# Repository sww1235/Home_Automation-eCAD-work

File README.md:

# Home_Automation-eCAD-work
Contains Eagle and KiCAD files used for custom circuit boards involved in my home automation systems

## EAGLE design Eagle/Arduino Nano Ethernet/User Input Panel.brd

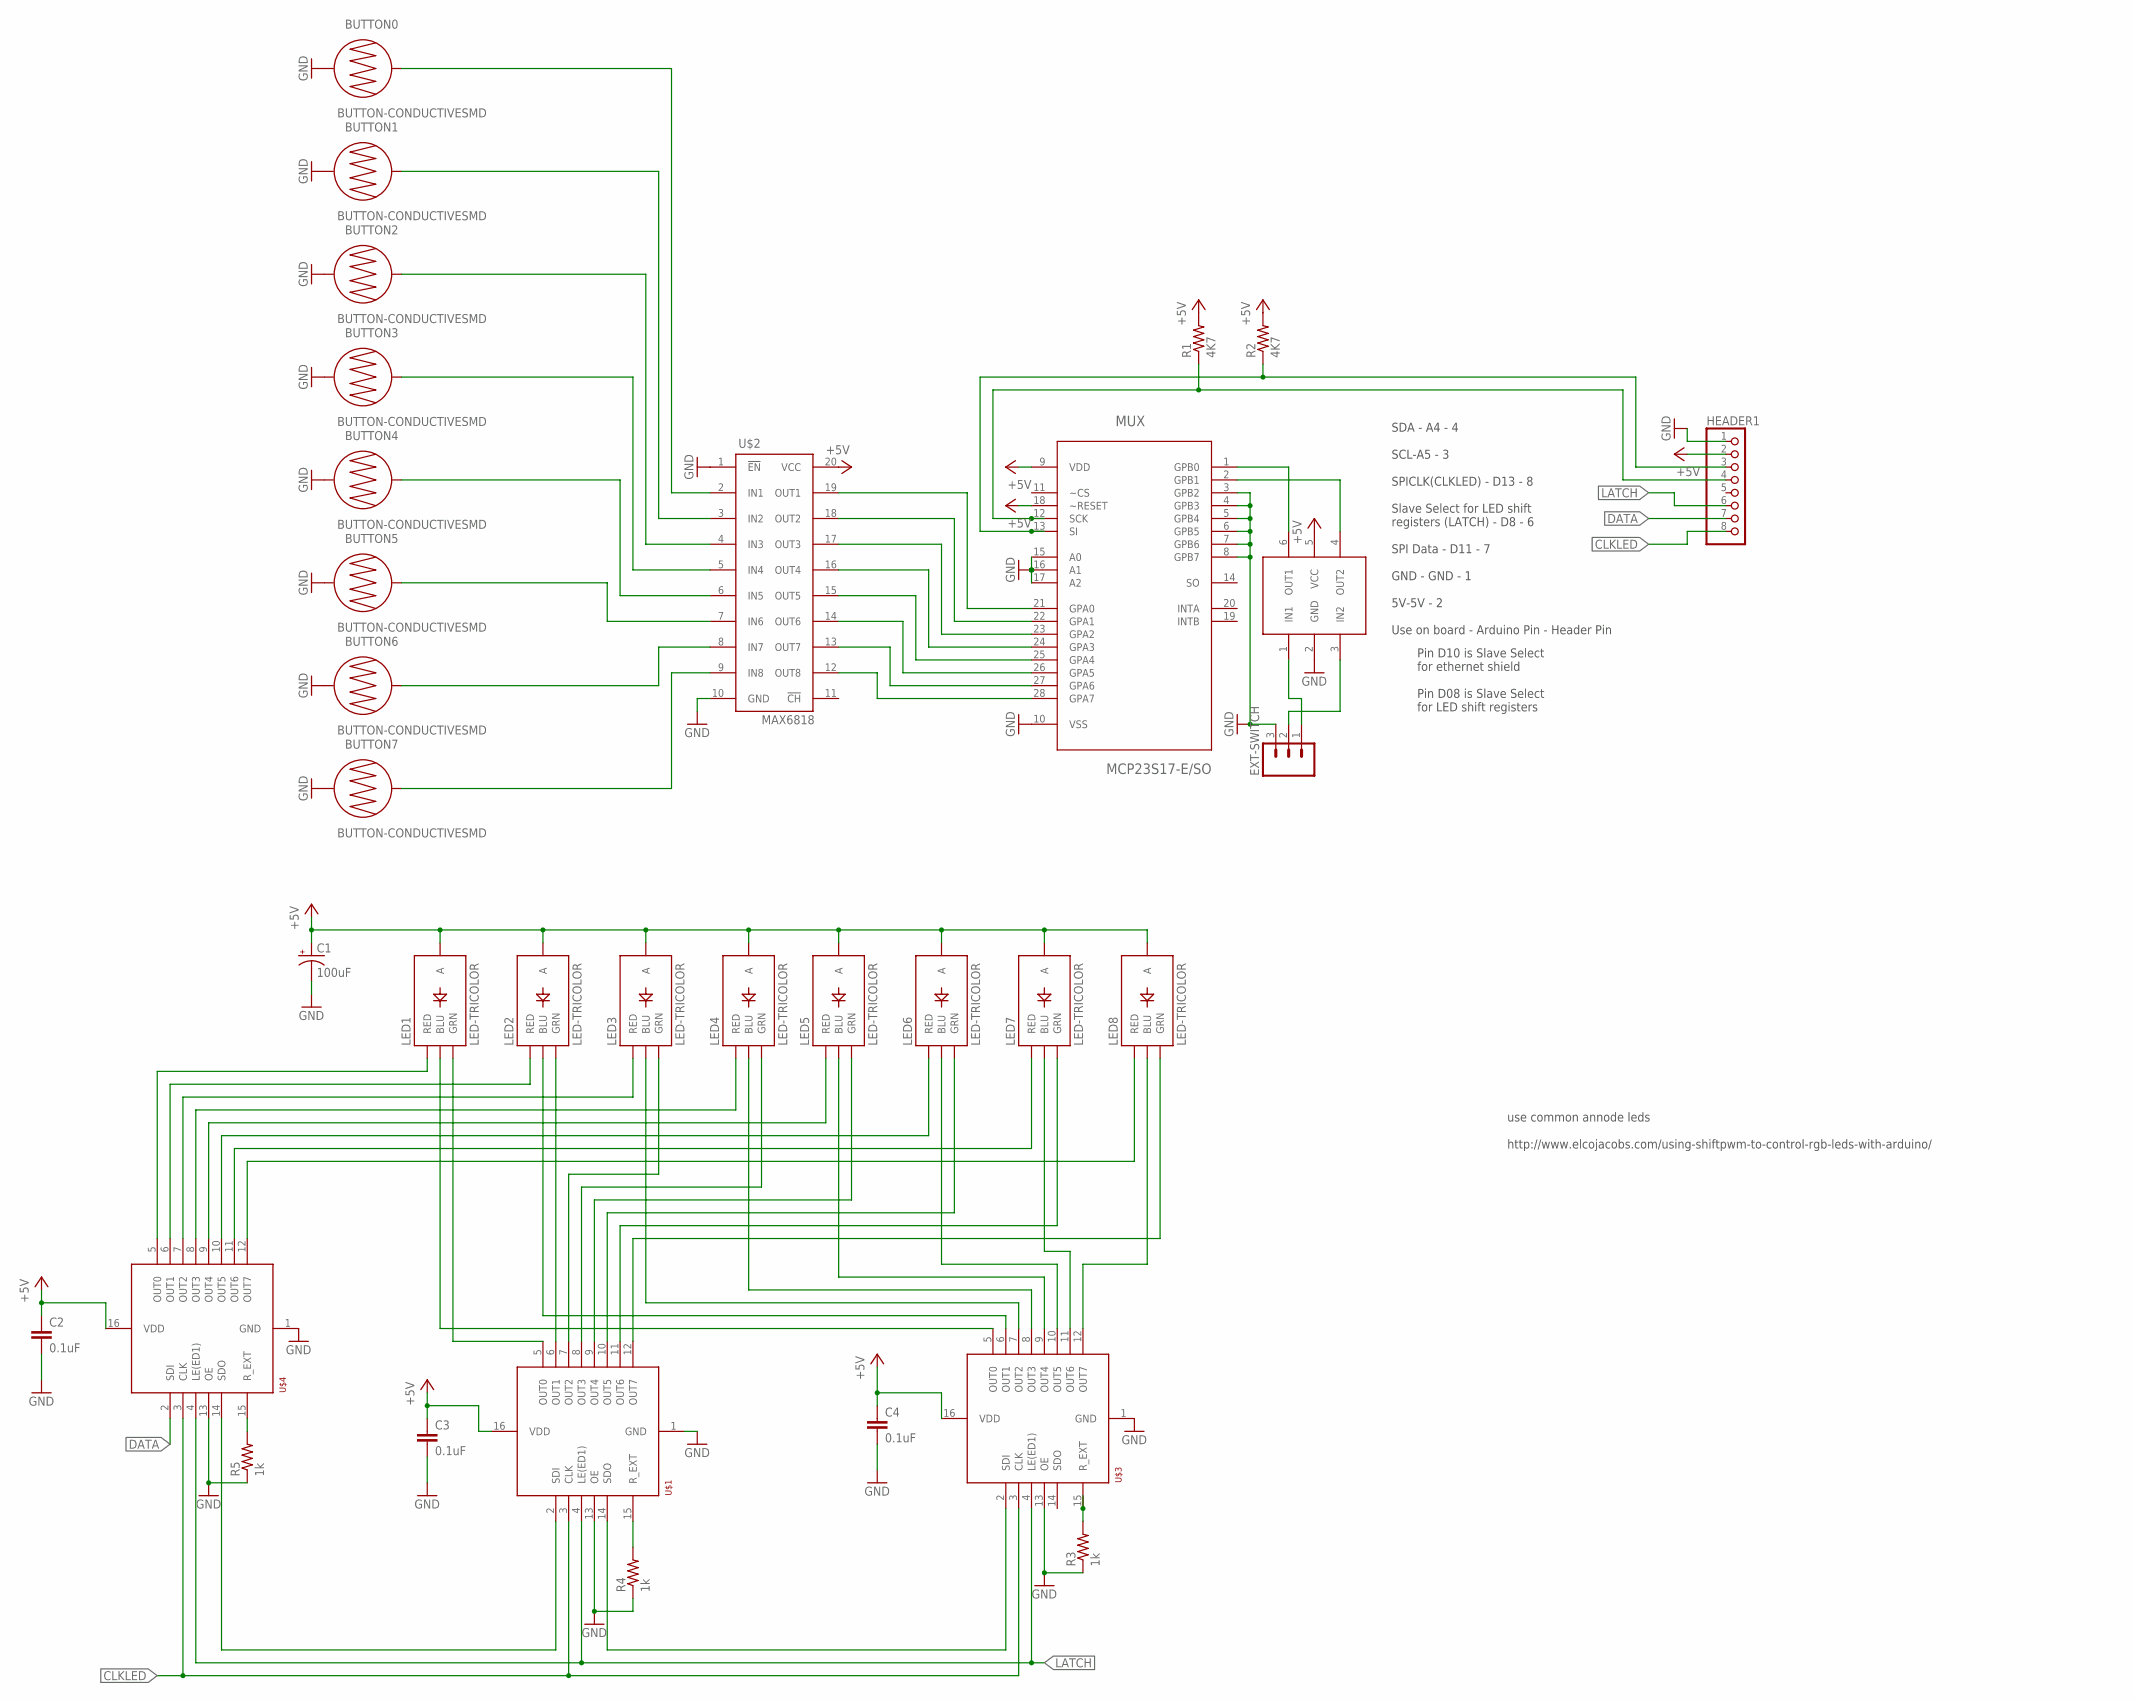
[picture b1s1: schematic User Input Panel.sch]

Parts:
BUTTON0, BUTTON1, BUTTON2, BUTTON3, BUTTON4, BUTTON5, BUTTON6, BUTTON7: BUTTON-CONDUCTIVESMD; BUTTON-CONDUCTIVE
C1: 100uF; EIA3216
C2, C3, C4: 0.1uF; 0402-CAP
EXT-SWITCH: M03-SCREW-5MM; SCREWTERMINAL-5MM-3
HEADER1: PINHD-1X8BIG; 1X08-BIG
LED1, LED2, LED3, LED4, LED5, LED6, LED7, LED8: LED-TRICOLOR; LED-TRICOLOR-SMD
MUX: MCP23S17-E/SO; SOIC127P030X265-28N
R1, R2: 4K7; 0204V
R3, R4, R5: 1k; 0402-RES
U$1, U$3, U$4: TLC5916/17; SOIC-16
U$2: MAX6818; SSOP20
U$5: MAX6817; SOT23-6L

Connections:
+5V: C1.A (+), C2.1, C3.1, C4.1, HEADER1.2, LED1.A, LED2.A, LED3.A, LED4.A, LED5.A, LED6.A, LED7.A, LED8.A, U$1.16 (VDD), U$2.20 (VCC), U$3.16 (VDD), U$4.16 (VDD), U$5.5 (VCC)
CLKLED: HEADER1.8, U$1.3 (CLK), U$3.3 (CLK), U$4.3 (CLK)
DATA: HEADER1.7, U$4.2 (SDI)
GND: BUTTON0.1, BUTTON1.1, BUTTON2.1, BUTTON3.1, BUTTON4.1, BUTTON5.1, BUTTON6.1, BUTTON7.1, C1.C (-), C2.2, C3.2, C4.2, EXT-SWITCH.3, HEADER1.1, MUX.3 (GPB2), MUX.4 (GPB3), MUX.5 (GPB4), MUX.6 (GPB5), MUX.7 (GPB6), MUX.8 (GPB7), MUX.10 (VSS), MUX.15 (A0), MUX.16 (A1), MUX.17 (A2), R3.1, R4.1, R5.1, U$1.1 (GND), U$1.13 (OE), U$2.1 (!EN!), U$2.10 (GND), U$3.1 (GND), U$3.13 (OE), U$4.1 (GND), U$4.13 (OE), U$5.2 (GND)
LATCH: HEADER1.6, U$1.4 (LE(ED1)), U$3.4 (LE(ED1)), U$4.4 (LE(ED1))
unnamed: MUX.28 (GPA7), U$2.12 (OUT8)
unnamed: MUX.24 (GPA3), U$2.16 (OUT4)
unnamed: MUX.26 (GPA5), U$2.14 (OUT6)
unnamed: MUX.25 (GPA4), U$2.15 (OUT5)
unnamed: MUX.27 (GPA6), U$2.13 (OUT7)
unnamed: MUX.23 (GPA2), U$2.17 (OUT3)
unnamed: MUX.22 (GPA1), U$2.18 (OUT2)
unnamed: MUX.21 (GPA0), U$2.19 (OUT1)
unnamed: HEADER1.4, MUX.12 (SCK), R1.1
unnamed: HEADER1.3, MUX.13 (SI), R2.1
unnamed: U$1.2 (SDI), U$4.14 (SDO)
unnamed: U$1.14 (SDO), U$3.2 (SDI)
unnamed: MUX.1 (GPB0), U$5.6 (OUT1)
unnamed: R5.2, U$4.15 (R_EXT)
unnamed: LED5.R (RED), U$4.9 (OUT4)
unnamed: LED6.R (RED), U$4.10 (OUT5)
unnamed: LED7.R (RED), U$4.11 (OUT6)
unnamed: R4.2, U$1.15 (R_EXT)
unnamed: R3.2, U$3.15 (R_EXT)
unnamed: LED1.R (RED), U$4.5 (OUT0)
unnamed: LED2.R (RED), U$4.6 (OUT1)
unnamed: LED3.R (RED), U$4.7 (OUT2)
unnamed: LED4.R (RED), U$4.8 (OUT3)
unnamed: LED8.R (RED), U$4.12 (OUT7)
unnamed: LED1.G (GRN), U$1.5 (OUT0)
unnamed: LED2.G (GRN), U$1.6 (OUT1)
unnamed: LED3.G (GRN), U$1.7 (OUT2)
unnamed: LED4.G (GRN), U$1.8 (OUT3)
unnamed: LED5.G (GRN), U$1.9 (OUT4)
unnamed: LED6.G (GRN), U$1.10 (OUT5)
unnamed: LED7.G (GRN), U$1.11 (OUT6)
unnamed: LED8.G (GRN), U$1.12 (OUT7)
unnamed: LED2.B (BLU), U$3.6 (OUT1)
unnamed: LED1.B (BLU), U$3.5 (OUT0)
unnamed: LED3.B (BLU), U$3.7 (OUT2)
unnamed: LED4.B (BLU), U$3.8 (OUT3)
unnamed: LED5.B (BLU), U$3.9 (OUT4)
unnamed: LED6.B (BLU), U$3.10 (OUT5)
unnamed: LED7.B (BLU), U$3.11 (OUT6)
unnamed: LED8.B (BLU), U$3.12 (OUT7)
unnamed: MUX.2 (GPB1), U$5.4 (OUT2)
unnamed: BUTTON0.2, U$2.2 (IN1)
unnamed: BUTTON1.2, U$2.3 (IN2)
unnamed: BUTTON2.2, U$2.4 (IN3)
unnamed: BUTTON3.2, U$2.5 (IN4)
unnamed: BUTTON4.2, U$2.6 (IN5)
unnamed: BUTTON5.2, U$2.7 (IN6)
unnamed: BUTTON7.2, U$2.9 (IN8)
unnamed: BUTTON6.2, U$2.8 (IN7)
unnamed: EXT-SWITCH.1, U$5.1 (IN1)
unnamed: EXT-SWITCH.2, U$5.3 (IN2)
VCC: MUX.9 (VDD), MUX.18 (~RESET), R1.2, R2.2

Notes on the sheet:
use common annode leds http://www.elcojacobs.com/using-shiftpwm-to-control-rgb-leds-with-arduino/
Pin D10 is Slave Select for ethernet shield Pin D08 is Slave Select for LED shift registers
SDA - A4 - 4 SCL-A5 - 3 SPICLK(CLKLED) - D13 - 8 Slave Select for LED shift registers (LATCH) - D8 - 6 SPI Data - D11 - 7 GND - GND - 1 5V-5V - 2 Use on board - Arduino Pin - Header Pin

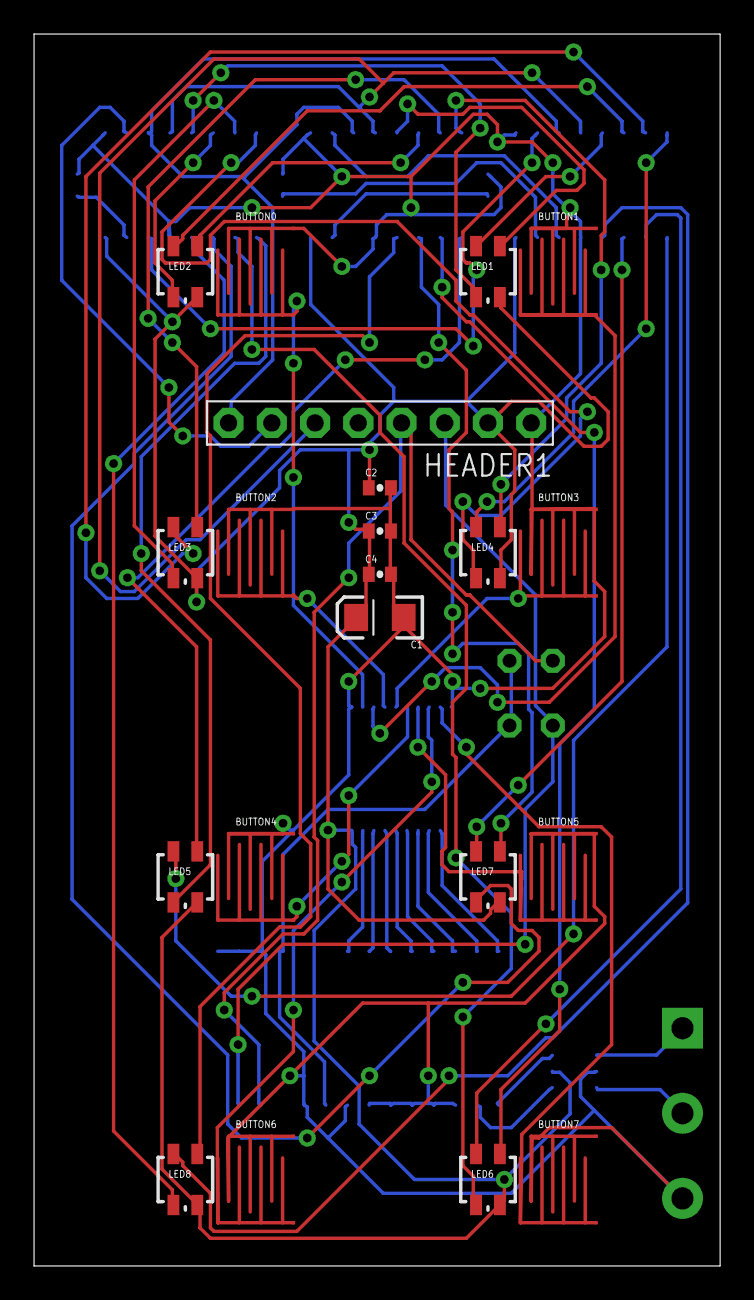
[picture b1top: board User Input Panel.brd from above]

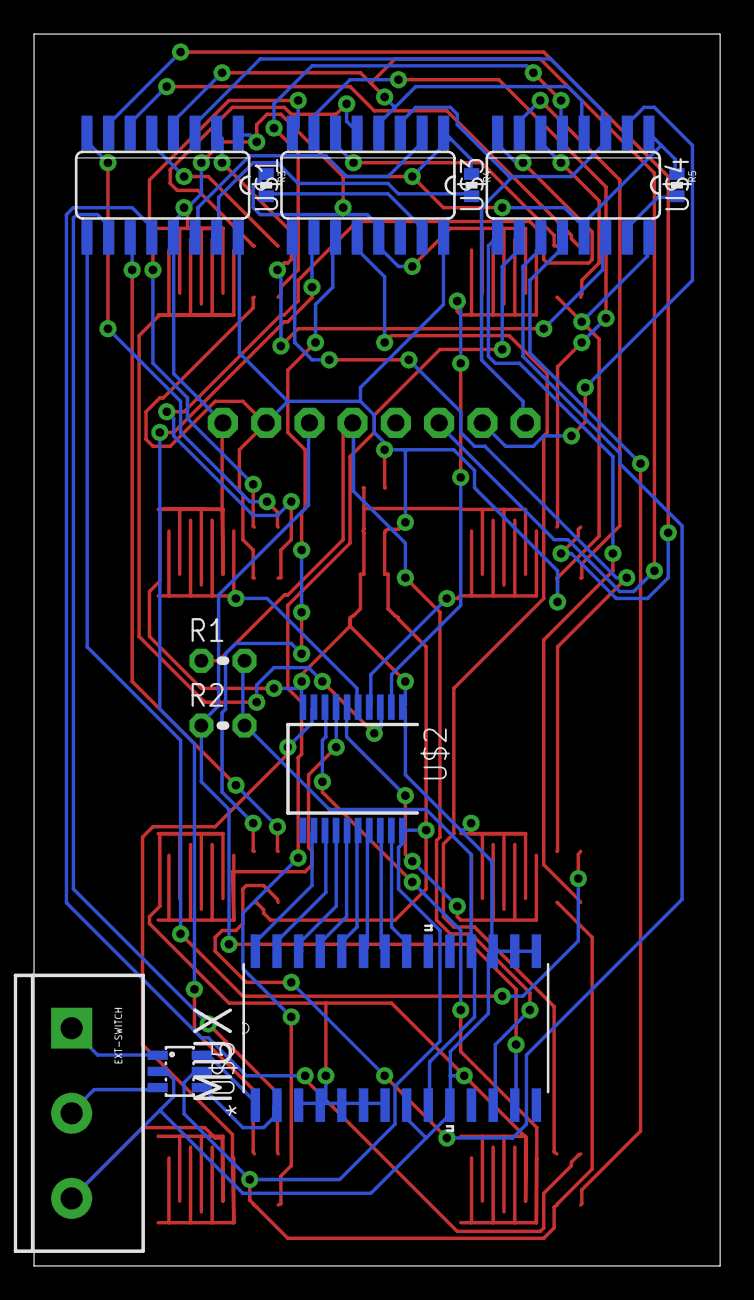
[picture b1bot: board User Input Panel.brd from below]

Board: 2 copper layers, 40.3 x 72.4 mm, 33 parts (12 on the bottom side), 57 nets.

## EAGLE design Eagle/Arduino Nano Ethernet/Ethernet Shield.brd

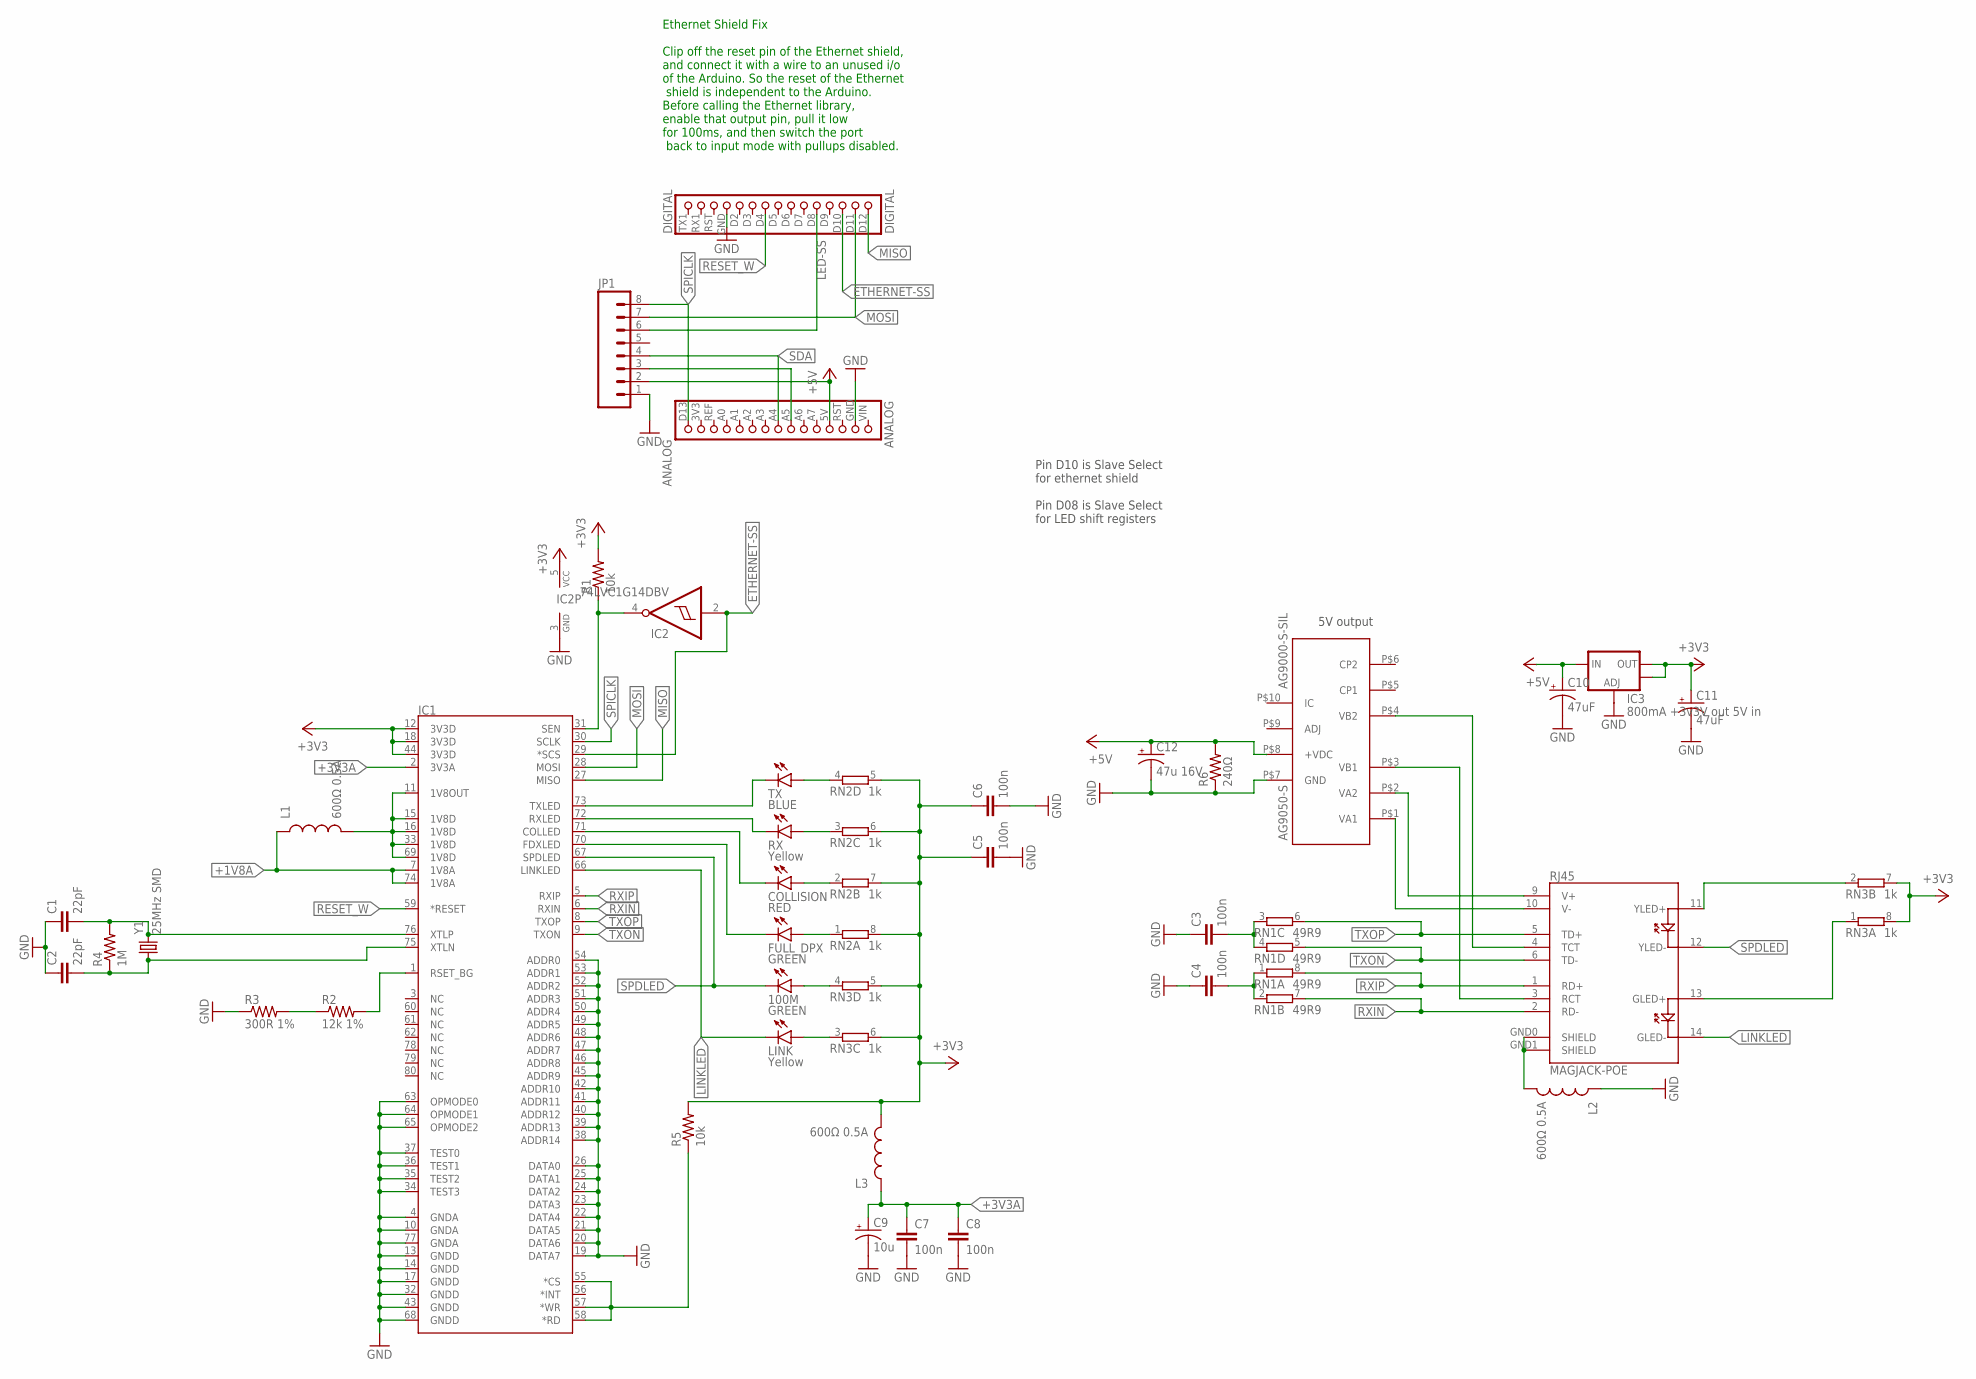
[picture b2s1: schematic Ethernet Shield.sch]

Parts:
100M: GREEN; LED-0603
AG9050-S: AG9000-S-SIL; AG9000-S
ANALOG: ANALOG; A1X15
C1, C2: 22pF; 0603-CAP
C3, C4, C5, C6, C7, C8: 100n; 0402-CAP
C9: 10u; EIA3216
C10, C11: 47uF; EIA3528
C12: 47u 16V; EIA3216
COLLISION: RED; LED-0603
DIGITAL: DIGITAL; 1X15
FULL_DPX: GREEN; LED-0603
IC1: W5100; LQFP-80
IC2: 74LVC1G14DBV; SOT23-5
IC3: 800mA +3v3V out 5V in; SOT223
JP1: M08; 1X08_ROUND
L1, L2, L3: 600Ω 0.5A; 0805
LINK: Yellow; LED-0603
R1, R5: 10k; 0402-RES
R2: 12k 1%; 0402-RES
R3: 300R 1%; 0402-RES
R4: 1M; 0402-RES
R6: 240Ω; 0402-RES
RJ45: MAGJACK-POE
RN1: 49R9; CAY16
RN2, RN3: 1k; CAY16
RX: Yellow; LED-0603
TX: BLUE; LED-0603
Y1: 25MHz SMD; HC49UP

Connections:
1V8: IC1.11 (1V8OUT), IC1.15 (1V8D), IC1.16 (1V8D), IC1.33 (1V8D), IC1.69 (1V8D), L1.2
+1V8A: IC1.7 (1V8A), IC1.74 (1V8A), L1.1
+3V3: C5.1, C6.1, C11.A (+), IC1.12 (3V3D), IC1.18 (3V3D), IC1.44 (3V3D), IC2.5 (VCC), IC3.2 (OUT), IC3.4 (OUT), L3.2, R1.2, R5.2, RN2.5 (2), RN2.6 (2), RN2.7 (2), RN2.8 (2), RN3.5 (2), RN3.6 (2), RN3.7 (2), RN3.8 (2)
+3V3A: C7.1, C8.1, C9.A (+), IC1.2 (3V3A), L3.1
+5V: AG9050-S.P$8 (+VDC), ANALOG.5V, C10.A (+), C12.A (+), IC3.3 (IN), JP1.2, R6.2
ETHERNET-SS: DIGITAL.D10, IC1.29 (*SCS), IC2.2 (I)
GND: AG9050-S.P$7 (GND), ANALOG.GND, C1.1, C2.1, C3.1, C4.1, C5.2, C6.2, C7.2, C8.2, C9.C (-), C10.C (-), C11.C (-), C12.C (-), DIGITAL.GND, IC1.4 (GNDA), IC1.10 (GNDA), IC1.13 (GNDD), IC1.14 (GNDD), IC1.17 (GNDD), IC1.19 (DATA7), IC1.20 (DATA6), IC1.21 (DATA5), IC1.22 (DATA4), IC1.23 (DATA3), IC1.24 (DATA2), IC1.25 (DATA1), IC1.26 (DATA0), IC1.32 (GNDD), IC1.34 (TEST3), IC1.35 (TEST2), IC1.36 (TEST1), IC1.37 (TEST0), IC1.38 (ADDR14), IC1.39 (ADDR13), IC1.40 (ADDR12), IC1.41 (ADDR11), IC1.42 (ADDR10), IC1.43 (GNDD), IC1.45 (ADDR9), IC1.46 (ADDR8), IC1.47 (ADDR7), IC1.48 (ADDR6), IC1.49 (ADDR5), IC1.50 (ADDR4), IC1.51 (ADDR3), IC1.52 (ADDR2), IC1.53 (ADDR1), IC1.54 (ADDR0), IC1.63 (OPMODE0), IC1.64 (OPMODE1), IC1.65 (OPMODE2), IC1.68 (GNDD), IC1.77 (GNDA), IC2.3 (GND), IC3.1 (ADJ), JP1.1, L2.1, R3.1, R6.1
LED-SS: DIGITAL.D8, JP1.6
LINKLED: IC1.66 (LINKLED), LINK.C, RJ45.14 (GLED-)
MISO: DIGITAL.D12, IC1.27 (MISO)
MOSI: DIGITAL.D11, IC1.28 (MOSI), JP1.7
unnamed: IC1.1 (RSET_BG), R2.2
unnamed: R2.1, R3.2
unnamed: C1.2, IC1.76 (XTLP), R4.2, Y1.2
unnamed: C2.2, IC1.75 (XTLN), R4.1, Y1.1
unnamed: L2.2, RJ45.GND0 (SHIELD), RJ45.GND1 (SHIELD)
unnamed: AG9050-S.P$1 (VA1), RJ45.10 (V-)
unnamed: AG9050-S.P$2 (VA2), RJ45.9 (V+)
unnamed: AG9050-S.P$4 (VB2), RJ45.4 (TCT)
unnamed: AG9050-S.P$3 (VB1), RJ45.3 (RCT)
unnamed: C3.2, RN1.3 (1), RN1.4 (1)
unnamed: C4.2, RN1.1, RN1.2 (1)
unnamed: COLLISION.C, IC1.71 (COLLED)
unnamed: FULL_DPX.C, IC1.70 (FDXLED)
unnamed: RJ45.11 (YLED+), RN3.2 (1)
unnamed: RJ45.13 (GLED+), RN3.1
unnamed: FULL_DPX.A, RN2.1
unnamed: COLLISION.A, RN2.2 (1)
unnamed: RN2.3 (1), RX.A
unnamed: RN2.4 (1), TX.A
unnamed: LINK.A, RN3.3 (1)
unnamed: 100M.A, RN3.4 (1)
unnamed: IC1.55 (*CS), IC1.57 (*WR), IC1.58 (*RD), R5.1
RESET_W: DIGITAL.D4, IC1.59 (*RESET)
RXIN: IC1.6 (RXIN), RJ45.2 (RD-), RN1.7 (2)
RXIP: IC1.5 (RXIP), RJ45.1 (RD+), RN1.8 (2)
RXLED: IC1.72 (RXLED), RX.C
SCL: ANALOG.A5, JP1.3
SDA: ANALOG.A4, JP1.4
SEN: IC1.31 (SEN), IC2.4 (O), R1.1
SPDLED: 100M.C, IC1.67 (SPDLED), RJ45.12 (YLED-)
SPICLK: ANALOG.D13, IC1.30 (SCLK), JP1.8
TXLED: IC1.73 (TXLED), TX.C
TXON: IC1.9 (TXON), RJ45.6 (TD-), RN1.5 (2)
TXOP: IC1.8 (TXOP), RJ45.5 (TD+), RN1.6 (2)

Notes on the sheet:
Pin D10 is Slave Select for ethernet shield Pin D08 is Slave Select for LED shift registers
5V output
Ethernet Shield Fix Clip off the reset pin of the Ethernet shield, and connect it with a wire to an unused i/o of the Arduino. So the reset of the Ethernet shield is independent to the Arduino. Before calling the Ethernet library, enable that output pin, pull it low for 100ms, and then switch the p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

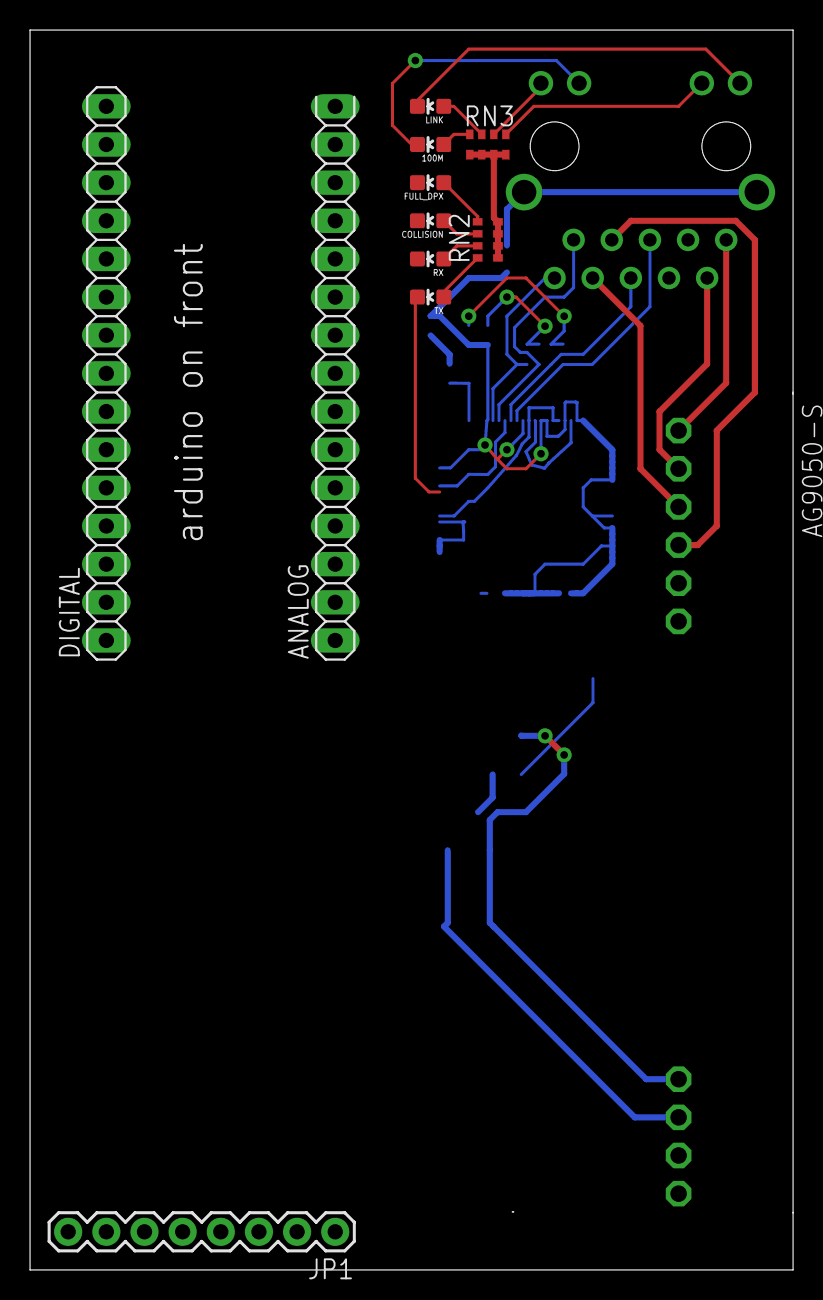
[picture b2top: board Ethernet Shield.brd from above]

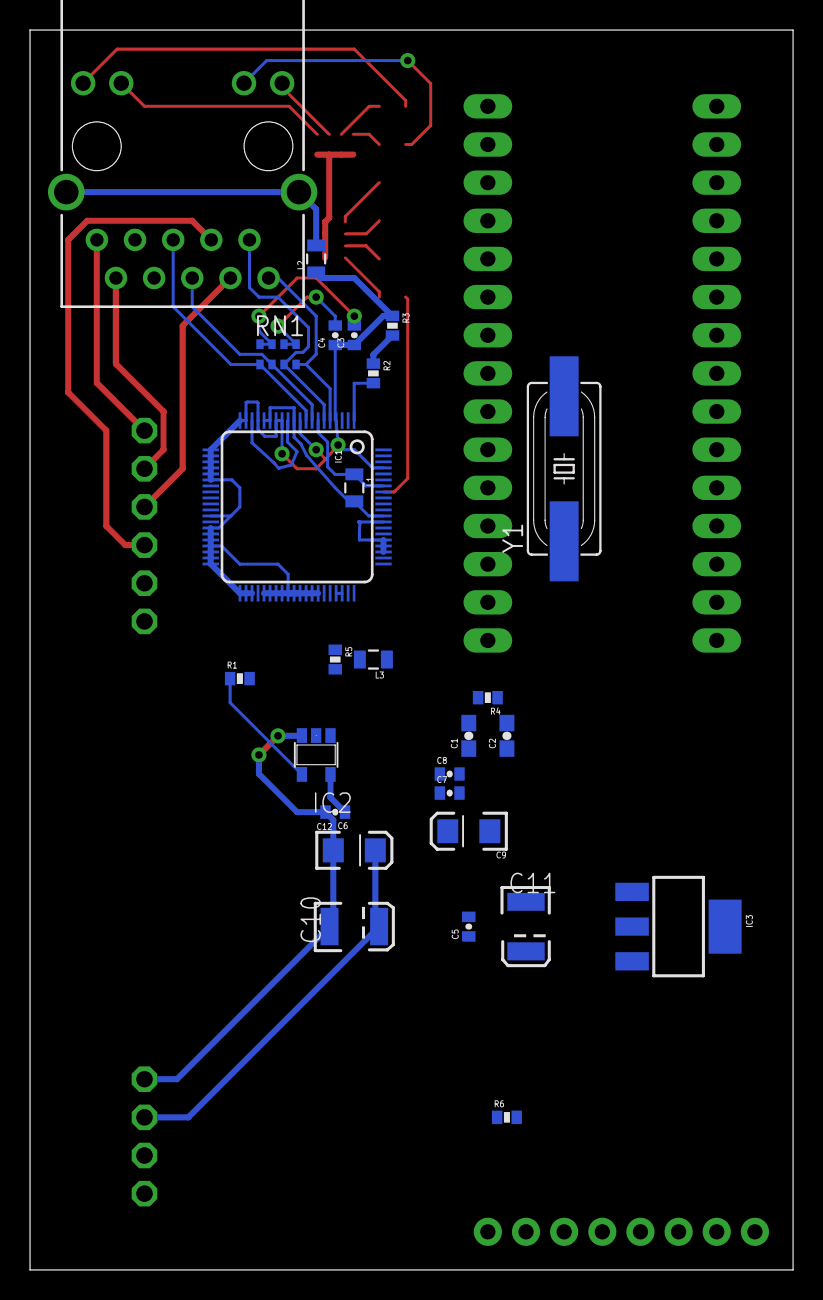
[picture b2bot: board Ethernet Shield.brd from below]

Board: 2 copper layers, 50.8 x 82.5 mm, 39 parts (27 on the bottom side), 45 nets.

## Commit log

2016-05-16 splitting repos

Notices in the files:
parts and their libraries:
SparkFun-DigitalIC: Licensing: Creative Commons ShareAlike 4.0 International - https://creativecommons.org/licenses/by-sa/4.0
